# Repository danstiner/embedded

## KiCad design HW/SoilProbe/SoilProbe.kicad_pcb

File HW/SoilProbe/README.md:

# Soil Probe 2026v1

Capacitive soil-moisture probe: a 20 x 126 mm 4-layer blade with the sensing electrodes buried
on the inner layers and a 80-130 MHz LC oscillator in the head. A host MCU (nRF54L15 node)
powers it for a few milliseconds and reads three things:

| Output | What it is | Used for |
|---|---|---|
| `FOUT` | oscillator frequency / 1024, 79 kHz (water) to 126 kHz (air) | volumetric water content |
| `REF - AMP` | oscillation amplitude detector, 8-80 mV | probe loss: bulk EC, salinity correction |
| `NTC` | 10 k thermistor at the soil line | soil temperature, water-permittivity correction |

Nothing has been built yet. Every number here is from simulation (`sim/soil_probe/`), and
`sim/soil_probe/TEST_PLAN.md` lists what to measure first. Design reasoning is in
`sim/soil_probe/DESIGN.md`.

## Predicted performance

| Item | Value | Source |
|---|---|---|
| Range | air to water; soil theta 0-0.6 | `system_sim.py` |
| Error, 2-point calibrated unit, generic medium curve | 1.4 % VWC sd (potting mix), 0.9 % (mineral soil), contact-limited | Monte Carlo, `system_sim.py` |
| Same unit without its own air/water calibration | 2.7 % VWC sd | Monte Carlo |
| Pore-water EC 0.5 to 3 dS/m, frequency only | +0.7 % VWC at theta 0.25, +3 % at 0.55 | error budget |
| Same, using the detector | under 0.1 % | error budget |
| Air gap 0.1 mm on one face | -1.9 % VWC at theta 0.25, -4.4 % at 0.40 | error budget |
| Bulk EC estimate | about +/-12 % (model; the detector is uncalibrated hardware) | Monte Carlo |
| Stops oscillating above | 16 mS probe loss: pore-water EC over about 4 dS/m in saturated potting mix (6 dS/m still runs at theta 0.45) | `characterize.py` |
| Supply | 3.0-3.6 V, about 26 mA for 4 ms per reading (about 100 uC) | datasheet sums |

The contact terms dominate and no circuit fixes them: install the blade in firm, undisturbed
or re-packed soil and do not rock it.

## Host interface (J1, 2.54 mm header pads, wires soldered and potted)

| Pin | Name | Direction | Notes |
|---|---|---|---|
| 1 | VDD | in | 3.0-3.6 V. The LDO is in dropout below 3.1 V, which is fine: frequency moves 190 ppm per 1.5 % of supply |
| 2 | EN | in | high = measure. 1 M pull-down on board |
| 3 | GND | | |
| 4 | NTC | out | 10 k B3380 to GND. Read against a host pull-up, ratiometric to host VDD |
| 5 | AMP | out | detector, 10 k source with 10 nF |
| 6 | REF | out | detector reference, 10 k source with 10 nF. Use `REF - AMP` |
| 7 | FOUT | out | 3.0 V CMOS square wave through 100 R |

Reading sequence:

1. EN high, wait 3.5 ms: LDO start-up is 2.8 ms max (TPS7A05 datasheet), the detector filter
   settles in 0.5 ms.
2. Time 64 periods of FOUT with a TIMER capture on a GPIOTE event (about 0.6 ms, 1e-4
   resolution at 16 MHz). Do not count edges in a TIMER through DPPI at MHz rates; that path
   drops events, which is why the prescaler divides all the way to 100 kHz.
3. Sample AMP, REF and NTC with the SAADC.
4. EN low. No FOUT edges within 1 ms of step 2 means the oscillator is stalled (soil too
   saline and wet): report that instead of a number.

Conversion (details and the reference model in `sim/soil_probe/scripts/system_sim.py`):

- per unit, once: store `f_air`, `f_water`, `det_air` from readings in air and in clean water;
- `x = (f^-2 - f_air^-2) / (f_water^-2 - f_air^-2)`, `q = (REF - AMP) / det_air`;
- `(x, q)` to permittivity and bulk EC through a 2-D table common to all units;
- permittivity to water content with the medium's mixing curve, using the water permittivity at
  the NTC temperature.

## Bill of materials

Passives are 0402 unless noted; any manufacturer.

| Ref | Value | Part | Notes |
|---|---|---|---|
| U1 | 3.0 V LDO, enable | TPS7A0530PDBVR | SOT-23-5. Power gate and regulator in one |
| U2 | 2.5 ns comparator | TLV3601DBVR | SOT-23-5. Squares the 0.1-0.4 V tank signal |
| U3, U4 | D flip-flop | SN74LVC1G80DBVR | SOT-23-5. Divide by 4; 160 MHz guaranteed |
| U5 | 12-stage ripple counter | SN74LV4040APWR | TSSOP-16. Q8 used, divide by 256 |
| Q1, Q2, Q3 | NPN RF, fT 8 GHz, Ccb 0.3 pF | BFR181 | SOT-23. Low Ccb and transit time set the loss pulling; do not substitute a general-purpose NPN |
| L1, L2 | 22 nH 2 %, Q >= 40 at 250 MHz | LQW18AN22NG00 | 0603 wirewound |
| C4 | 33 pF C0G 2 % | any | tank capacitor |
| R3 | 15 R 1 % | any | in series with C4: damps the strip line's second resonance |
| R4, R5, R7 | 22 R 1 % | any | base stoppers |
| R6 | 560 R 1 % | any | tail current, 3.1 mA |
| R8 | 1.1 k 1 % | any | reference transistor at half the tail current |
| R2 | 100 R 1 % | any | collector feed, sets the comparator common mode |
| R11, R12, R13 | 100 R | any | comparator input isolation, FOUT series |
| R9, R10 | 10 k | any | detector filters |
| R1 | 1 M | any | EN pull-down |
| C3, C5, C6 | 10 nF | any | |
| C7-C10 | 100 nF | any | |
| C1, C2 | 1 uF 0603 | any | LDO in and out |
| TH1 | 10 k NTC 1 %, B 3380 | NCP15XH103F03RC | |
| J1 | 1x7 2.54 mm pads | none | solder wires |

## Fabrication

OSH Park 4-layer: FR408HR, 0.2 mm 2113 prepreg over the inner layers, ENIG. The board stackup
in the `.kicad_pcb` matches their published one, and the design rules in the `.kicad_pro` are
their 4-layer limits (5 mil track and space, 10 mil drill, 4 mil annular ring, 10 mil hole to
inner copper).

The prepreg is part of the sensor: it is the 0.2 mm insulation between electrode and soil, and
its thickness tolerance (+/-10 %) is the main unit-to-unit term left after calibration (about
0.5 % VWC). A fab with a different outer prepreg works but shifts the common table: rerun the
simulation with that stack.

The sensing area has no copper on the outer layers and no vias, so nothing metallic touches
the soil even if the mask is scratched.

## Assembly and potting

- Parts are on the front only. There are no reference designators on the silkscreen (no room
  between the 0402s); use the fab layer or the interactive placement in KiCad.
- Pot the head on both faces down to the SOIL LINE mark. The simulation assumes potting
  compound (relative permittivity about 3.5) over the 6 mm of strip above the soil line; the
  two-point calibration absorbs the difference if you use something else, as long as it is
  applied before calibrating.
- Seal the board edges of the blade (conformal coat or a thin epoxy wipe). The strips stop 1 mm
  short of the edge, but exposed FR-4 edges wick water along the glass weave over time.
- Calibrate after potting: one reading in air, one with the blade in clean water up to the soil
  line.

## Bring-up, before any soil

Predicted values from `sim/soil_probe/scripts/expected_liquids.py`:

| Medium | FOUT | REF - AMP |
|---|---|---|
| air | 126.0 kHz | 40 mV |
| isopropanol 99 % | 102.1 kHz | 60 mV |
| tap water (0.3 mS/cm) | 79.6 kHz | 62 mV |
| 1 g/L salt water | 77.9 kHz | 20 mV |

Absolute frequency depends on stray capacitance that the simulation only estimates (2.5 pF per
tank node); expect the air value within +/-5 %. The ratios between media are the real test. If
FOUT in air is above 137 kHz the first flip-flop is being clocked past 140 MHz: raise C4.

Never probe the tank nodes (SA, SB) with a scope probe; 10 pF moves the oscillator 10 %. Look
at FOUT, or at the comparator output with a low-capacitance probe.

## Files

| Path | Contents |
|---|---|
| `SoilProbe.kicad_sch`, `.kicad_pcb`, `.kicad_pro` | KiCad 10 project. ERC and DRC (with schematic parity) are clean |
| `Components/SoilProbe.kicad_sym` | comparator and probe-strip symbols |
| `sim/soil_probe/` | field solver, probe line model, ngspice oscillator model, system simulation, design notes, test plan |

The schematic and board were generated by script from one netlist and then checked with
`kicad-cli`; they are ordinary KiCad files and are meant to be edited by hand from here on.

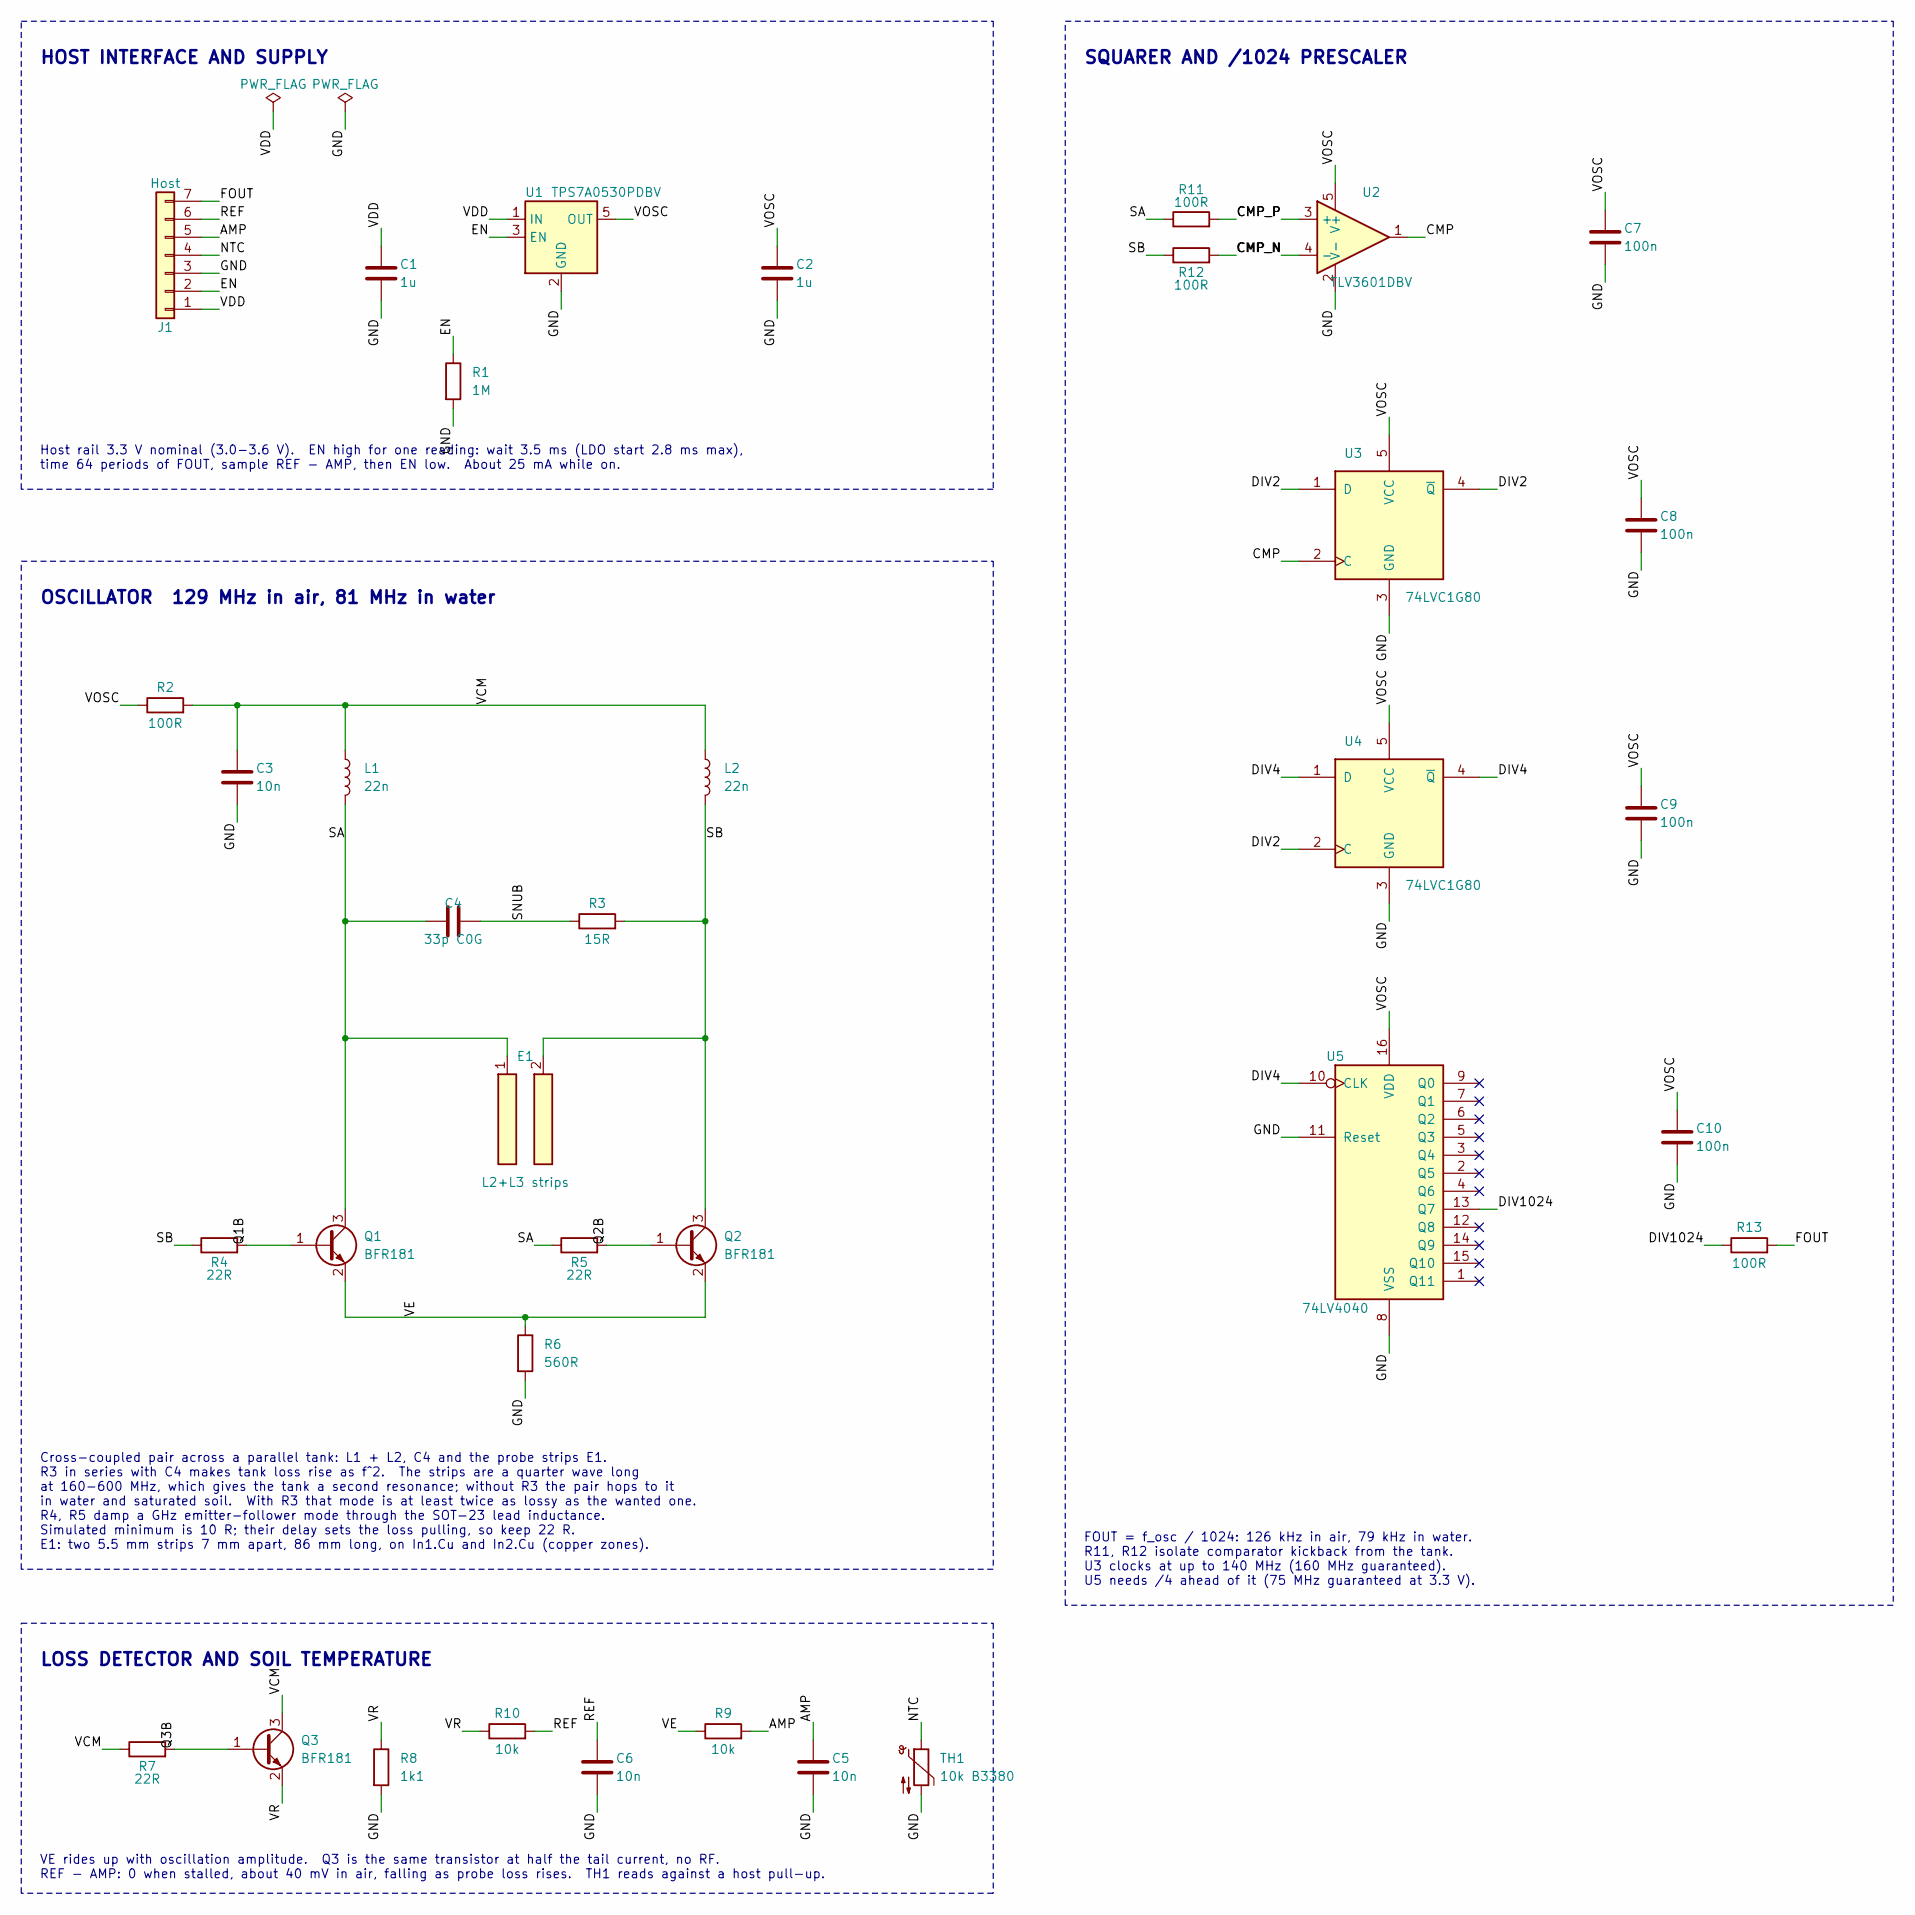
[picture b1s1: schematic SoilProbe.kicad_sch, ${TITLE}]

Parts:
C1, C2: 1u; C_0603_1608Metric
C3, C5, C6: 10n; C_0402_1005Metric
C4: 33p C0G; C_0402_1005Metric; Tolerance 2%
C7, C8, C9, C10: 100n; C_0402_1005Metric
E1: L2+L3 strips
J1: Host; PinHeader_1x07_P2.54mm_Vertical
L1, L2: 22n; L_0603_1608Metric; Tolerance 2%; MPN LQW18AN22NG00D
Q1, Q2, Q3: BFR181; SOT-23; MPN BFR181E6327HTSA1
R1: 1M; R_0402_1005Metric
R2: 100R; R_0402_1005Metric; Tolerance 1%
R3: 15R; R_0402_1005Metric; Tolerance 1%
R4, R5, R7: 22R; R_0402_1005Metric; Tolerance 1%
R6: 560R; R_0402_1005Metric; Tolerance 1%
R8: 1k1; R_0402_1005Metric; Tolerance 1%
R9, R10: 10k; R_0402_1005Metric
R11, R12, R13: 100R; R_0402_1005Metric
TH1: 10k B3380; R_0402_1005Metric; Tolerance 1%; MPN NCP15XH103F03RC
U1: TPS7A0530PDBV; SOT-23-5; MPN TPS7A0530PDBVR
U2: TLV3601DBV; SOT-23-5; MPN TLV3601DBVR
U3, U4: 74LVC1G80; SOT-23-5; MPN SN74LVC1G80DBVR
U5: 74LV4040; TSSOP-16_4.4x5mm_P0.65mm; MPN SN74LV4040APWR

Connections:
/AMP: C5.1, J1.5, R9.2
/CMP: U2.1, U3.2 (C)
/CMP_N: R12.2, U2.4 (-)
/CMP_P: R11.2, U2.3 (+)
/DIV2: U3.1 (D), U3.4 (~Q), U4.2 (C)
/DIV4: U4.1 (D), U4.4 (~Q), U5.10 (CLK)
/DIV1024: R13.1, U5.13 (Q7)
/EN: J1.2, R1.1, U1.3 (EN)
/FOUT: J1.7, R13.2
/GND: C1.2, C2.2, C3.2, C5.2, C6.2, C7.2, C8.2, C9.2, C10.2, J1.3, R1.2, R6.2, R8.2, TH1.2, U1.2 (GND), U2.2 (V-), U3.3 (GND), U4.3 (GND), U5.8 (VSS), U5.11 (Reset)
/NTC: J1.4, TH1.1
/Q1B: Q1.1 (B), R4.2
/Q2B: Q2.1 (B), R5.2
/Q3B: Q3.1 (B), R7.2
/REF: C6.1, J1.6, R10.2
/SA: C4.1, E1.1 (A), L1.2, Q1.3 (C), R5.1, R11.1
/SB: E1.2 (B), L2.2, Q2.3 (C), R3.2, R4.1, R12.1
/SNUB: C4.2, R3.1
/VCM: C3.1, L1.1, L2.1, Q3.3 (C), R2.2, R7.1
/VDD: C1.1, J1.1, U1.1 (IN)
/VE: Q1.2 (E), Q2.2 (E), R6.1, R9.1
/VOSC: C2.1, C7.1, C8.1, C9.1, C10.1, R2.1, U1.5 (OUT), U2.5 (V+), U3.5 (VCC), U4.5 (VCC), U5.16 (VDD)
/VR: Q3.2 (E), R8.1, R10.1

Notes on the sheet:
HOST INTERFACE AND SUPPLY
Host rail 3.3 V nominal (3.0-3.6 V). EN high for one reading: wait 3.5 ms (LDO start 2.8 ms max), time 64 periods of FOUT, sample REF - AMP, then EN low. About 25 mA while on.
OSCILLATOR 129 MHz in air, 81 MHz in water
Cross-coupled pair across a parallel tank: L1 + L2, C4 and the probe strips E1. R3 in series with C4 makes tank loss rise as f^2. The strips are a quarter wave long at 160-600 MHz, which gives the tank a second resonance; without R3 the pair hops to it in water and saturated soil. With R3 that mode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
LOSS DETECTOR AND SOIL TEMPERATURE
VE rides up with oscillation amplitude. Q3 is the same transistor at half the tail current, no RF. REF - AMP: 0 when stalled, about 40 mV in air, falling as probe loss rises. TH1 reads against a host pull-up.
SQUARER AND /1024 PRESCALER
FOUT = f_osc / 1024: 126 kHz in air, 79 kHz in water. R11, R12 isolate comparator kickback from the tank. U3 clocks at up to 140 MHz (160 MHz guaranteed). U5 needs /4 ahead of it (75 MHz guaranteed at 3.3 V).

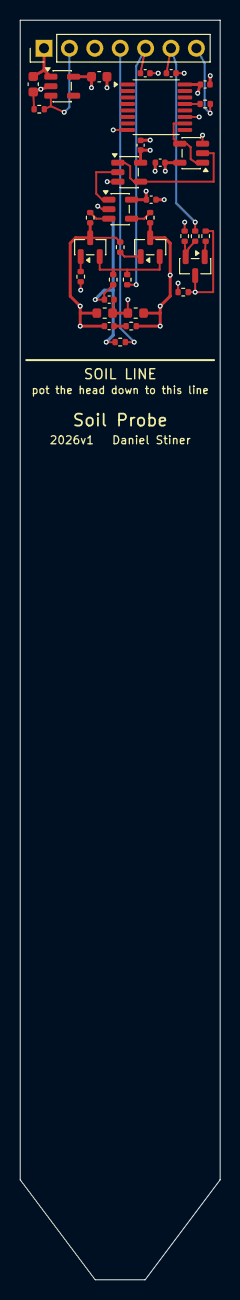
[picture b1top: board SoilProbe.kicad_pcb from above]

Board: 4 copper layers, 20.0 x 126.0 mm, 35 parts (0 on the bottom side), 23 nets.

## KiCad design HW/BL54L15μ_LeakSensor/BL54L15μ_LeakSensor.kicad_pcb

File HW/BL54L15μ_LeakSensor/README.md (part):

# Leak sensor

## 1. Scope

Battery-powered leak and humidity sensor built on the Ezurio BL54L15μ (nRF54L15) module.
Two contacts on the bottom detect water, immediately triggering a report over Matter
and optionally an alarm buzzer. An SHT40 measures temperature and humidity for mold detection.

The board stands on the end of a CR2 cell in a printed case. Two metal pins in the case's
floor touch the water and press on two dome contacts on the board (5.7).

This is revision **2026v5**, ordered on 2026-11-23 (tag `fab/BL54L15μ-leak-sensor/2026v5`)
and not yet assembled. The baseline is 2026v4, the first leak board,
fabricated as the hygrometer's 2026v4 (tag `fab/BL54L15μ-hygrometer/2026v4`, firmware
board `bl54l15u_hygrometer@2026v4`).

## 2. Changes from 2026v4

| Item          | 2026v4                                   | 2026v5                                                  |
| ------------- | ---------------------------------------- | ------------------------------------------------------- |
| Size          | 48 mm circle                             | 18 × 16 mm, stands on the end of the cell (5.6)         |
| Battery       | CR2 in a Keystone 1011 holder            | CR2 on wires to two pads on the back                    |
| Leak contacts | 6 mm domes on the back, driven one way   | 4 mm domes on the front, driven either way (4.1)        |
| Leak pins     | drive P0.01, sense P1.07, 1 MΩ to ground | P1.12 and P1.11 each drive or sense; 1 MΩ to a GPIO     |
| Sensor        | SHT45                                    | SHT40 (5.3)                                             |
| I2C           | SDA P1.14, SCL P1.04                     | unchanged                                               |
| Buzzer        | 8.5 mm, never driven by firmware         | 5 mm, on P1.05, smaller driver parts (5.5)              |
| SWD           | 2×5 1.27 mm box header on the front      | 2×5 1.27 mm pads on the back: header or pogo clip (4.2) |
| Mounting      | two holes                                | none; the case holds the board by its edge              |

## 3. Requirements

| ID  | Requirement                                                                             |
| --- | --------------------------------------------------------------------------------------- |
| R-1 | Wake on water across the contacts: Edge triggered, not polling                          |
| R-2 | Last 5 years on one CR2 (850 mAh): average current under 15 µA assuming 20% derating    |
| R-3 | Minimize probe corrosion: alternate probe voltage                                       |
| R-4 | Confirm water by measuring resistance with the SAADC, in both directions                |
| R-5 | Temperature and humidity reports from SHT4x over I2C with MCU pull-ups                  |
| R-6 | Minimize case size with small board standing on the end of a CR2 (Ø15.6 max)            |
| R-7 | SWD through a soldered 2×5 1.27 mm header or a pogo-pin clip from the side              |
| R-8 | Front parts in one reflow pass; the back has only pads and optional parts (J1, JP1, C3) |
| R-9 | A buzzer that can optionally sound when it finds water, >=60 dBA at 1 m                 |

## 4. Design trades

### 4.1 Leak front end

2026v4 drives one contact through 10 kΩ and senses the other through 10 kΩ, with 1 MΩ to
ground. While dry the drive is held high: no current flows, and a rising edge on the sense
pin wakes the board. Current always flows the same way, which polarizes the contacts and
corrodes the anode. Conductivity cells are driven with alternating polarity for this
reason (Lee and Kester, Analog Dialogue 50-11).

2026v5 makes both sides identical, so either can drive and either can sense:

- **1 MΩ returned to a GPIO, not ground.** While armed, the driving side's 1 MΩ would
  otherwise sit across the cell and draw 3 µA, 20 % of R-2. With its return pin at the
  same level as the drive it draws nothing.
- **Two return pins, not one.** One shared return cannot sit high for the driving side and
  low for the sensing side at the same time.
- **External pull-down.** At the nRF54L15's 13 kΩ typical internal pull-down (Ezurio
  datasheet, I2C note) the sense node could never reach the input-high level through
  20 kΩ of series resistance.
- **Both sense pins analog-capable** (AIN5, AIN4), since each side senses in one direction.

### 4.2 Debug connector

A 2×5 1.27 mm box header (CNC Tech 3220-10-0300-00, 4.9 mm tall) on the back would hold
the cell 5 mm off the board. So J1 is a set of pads that takes either that header,
hand-soldered on the first few boards, or a pogo-pin clip clamped on from the left edge.
The case is sized for boards without the header.

Standard header land patterns start at the pin rows, 0.635 mm off center, and run outward
under the bent tails: 0.63 to 3.40 mm in the header's datasheet, 0.75 to 3.15 mm in
KiCad's stock footprint. A clip whose rows are 1.27 mm apart would land on the very ends
of those pads. J1's pads start 0.3 mm off center, so they take clip rows 1.27 or 2.54 mm
apart as well as the header's tails (`Components/LeakSensor.pretty`). The pads on the
edge side stop at 2.6 mm to keep copper 0.381 mm from the edge; the header's tails
overhang them by about 0.15 mm, with no fillet at the toe.

BZ1 sits on the front directly opposite J1, so the clip's other jaw rests on its flat
top. No keep-out is reserved for the clip: it presses lightly and tolerates an uneven
bite.

### 4.3 Supply

The CR2 feeds everything directly: the module takes 1.7 to 3.5 V (Ezurio datasheet 0.7,
table 3) and the SHT40 1.08 to 3.6 V. The firmware reads the cell through the SAADC's VDD
input. There is no reverse-polarity protection; the wires are soldered once.

## 5. Circuit

### 5.1 Leak front end: P1, P2, D1, D2, R1–R4

```
P1 ── ELEC_A ──┬── R1 10 kΩ ── LEAK_A (P1.12, AIN5) ── R3 1 MΩ ── LEAK_A_RET (P1.09)
               D1 TPD1E10B06 to GND
P2 ── ELEC_B ──┬── R2 10 kΩ ── LEAK_B (P1.11, AIN4) ── R4 1 MΩ ── LEAK_B_RET (P1.10)
               D2 TPD1E10B06 to GND
```

| State (A to B; B to A swaps the sides) | LEAK_A   | LEAK_A_RET | LEAK_B           | LEAK_B_RET | Current while dry |
| -------------------------------------- | -------- | ---------- | ---------------- | ---------- | ----------------- |
| Armed                                  | out high | out high   | input, edge wake | out low    | none              |
| Measure                                | out high | out high   | SAADC            | out low    | none              |
| Parked (after water is found)          | out low  | out low    | out low          | out low    | none              |

- **Wake threshold.** The sensing node sits at VDD × R4 / (R4 + R1 + R2 + R_water), which
  does not depend on the cell voltage. With V_IH = 0.7 VDD (to be confirmed in the nRF54L15
  datasheet) the edge fires below about 0.41 MΩ between the contacts.
- **SAADC.** The same divider reads 0.27 V at 10 MΩ, so damp contacts well above the wake
  threshold are still seen (`CONFIG_APP_LEAK_THRESHOLD_MV`). Averaging the two directions
  cancels the contacts' polarization offset.
- **Wet and armed**, at most VDD / 1.02 MΩ ≈ 3 µA flows one way until the firmware parks
  the pins.
- R1 and R2 limit current into the pins; D1 and D2 clamp ESD at the contacts.

### 5.2 MCU module: Ezurio 453-00223R (IC1)

| Pad    | nRF54L15      | Net        | Use                                               |
| ------ | ------------- | ---------- | ------------------------------------------------- |
| 5      | VDD           | VDD        | C2 10 µF, the one capacitor Ezurio requires (5.1) |
| 19     | P1.12 / AIN5  | LEAK_A     | Contact A: drive, edge wake, SAADC                |
| 23     | P1.11 / AIN4  | LEAK_B     | Contact B                                         |
| 22     | P1.09         | LEAK_A_RET | R3's return                                       |
| 21     | P1.10         | LEAK_B_RET | R4's return                                       |
| 18, 17 | P1.14, P1.04  | SDA, SCL   | U1 (firmware `i2c21`), internal pull-ups          |
| 15     | P1.05         | BUZZ       | Q1's gate: BZ1 at 4 kHz (5.5)                     |
| 12, 10 | P1.00, P1.01  | XL1, XL2   | X1, 32.768 kHz, internal load capacitors          |
| 27, 25 | SWDIO, SWDCLK | –          | J1 2, 4                                           |
| 32     | nRESET        | –          | J1 10                                             |
| 42     | P2.07         | SWO        | J1 6                                              |

- **Nordic's pin rules** decide which pins can be used: a peripheral reaches pins of its
  own port only, so I2C and PWM are on port 1; port 2 cannot wake the chip; SCL must be on
  a clock pin (Nordic DevZone, section 9). Within those rules the pads are taken in the
  order the traces leave the module: I2C toward U1, then the leak nets.
- **LEAK_A_RET** takes inner pad 22 and a via under the module, as a fourth net cannot
  leave the bottom pad row on the front. It is a static line.
- **Analog channels.** The AIN numbers are from the Ezurio pin table. 2026v4 confirmed
  P1.07 = AIN3 on hardware; AIN4 and AIN5 are unconfirmed (section 8). A wrong channel
  reads near VDD, which looks like a leak.
- **Firmware** sees this in a new board revision's overlay: the leak node's four pins and
  two SAADC channels, and the buzzer as a PWM on P1.05. The I2C pins are 2026v4's.
- All other pins are open and flagged no-connect. The module's DC/DC inductor is inside.

### 5.3 Temperature and humidity: SHT40-AD1F (U1)

U1 is at address 0x44 with C1 100 nF beside it, on I2C through the module's 13 kΩ
pull-ups. It is typically within ±1.8 %RH and ±0.2 °C (SHT4x datasheet, tables 1 and 2),
enough to watch for mold; 2026v4's SHT45 was more accurate than needed. The AD1F version
has a membrane over the sensor opening. Idle current is 0.08 µA typical (table 4).

Self-heating is negligible: the board averages about 0.05 mW. What matters is how freely
room air reaches U1. The case has one small vent beside it (5.7), so U1 follows the room
slowly. BZ1 is 2 mm away, so an alarm warms U1 for some minutes (7.1).

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
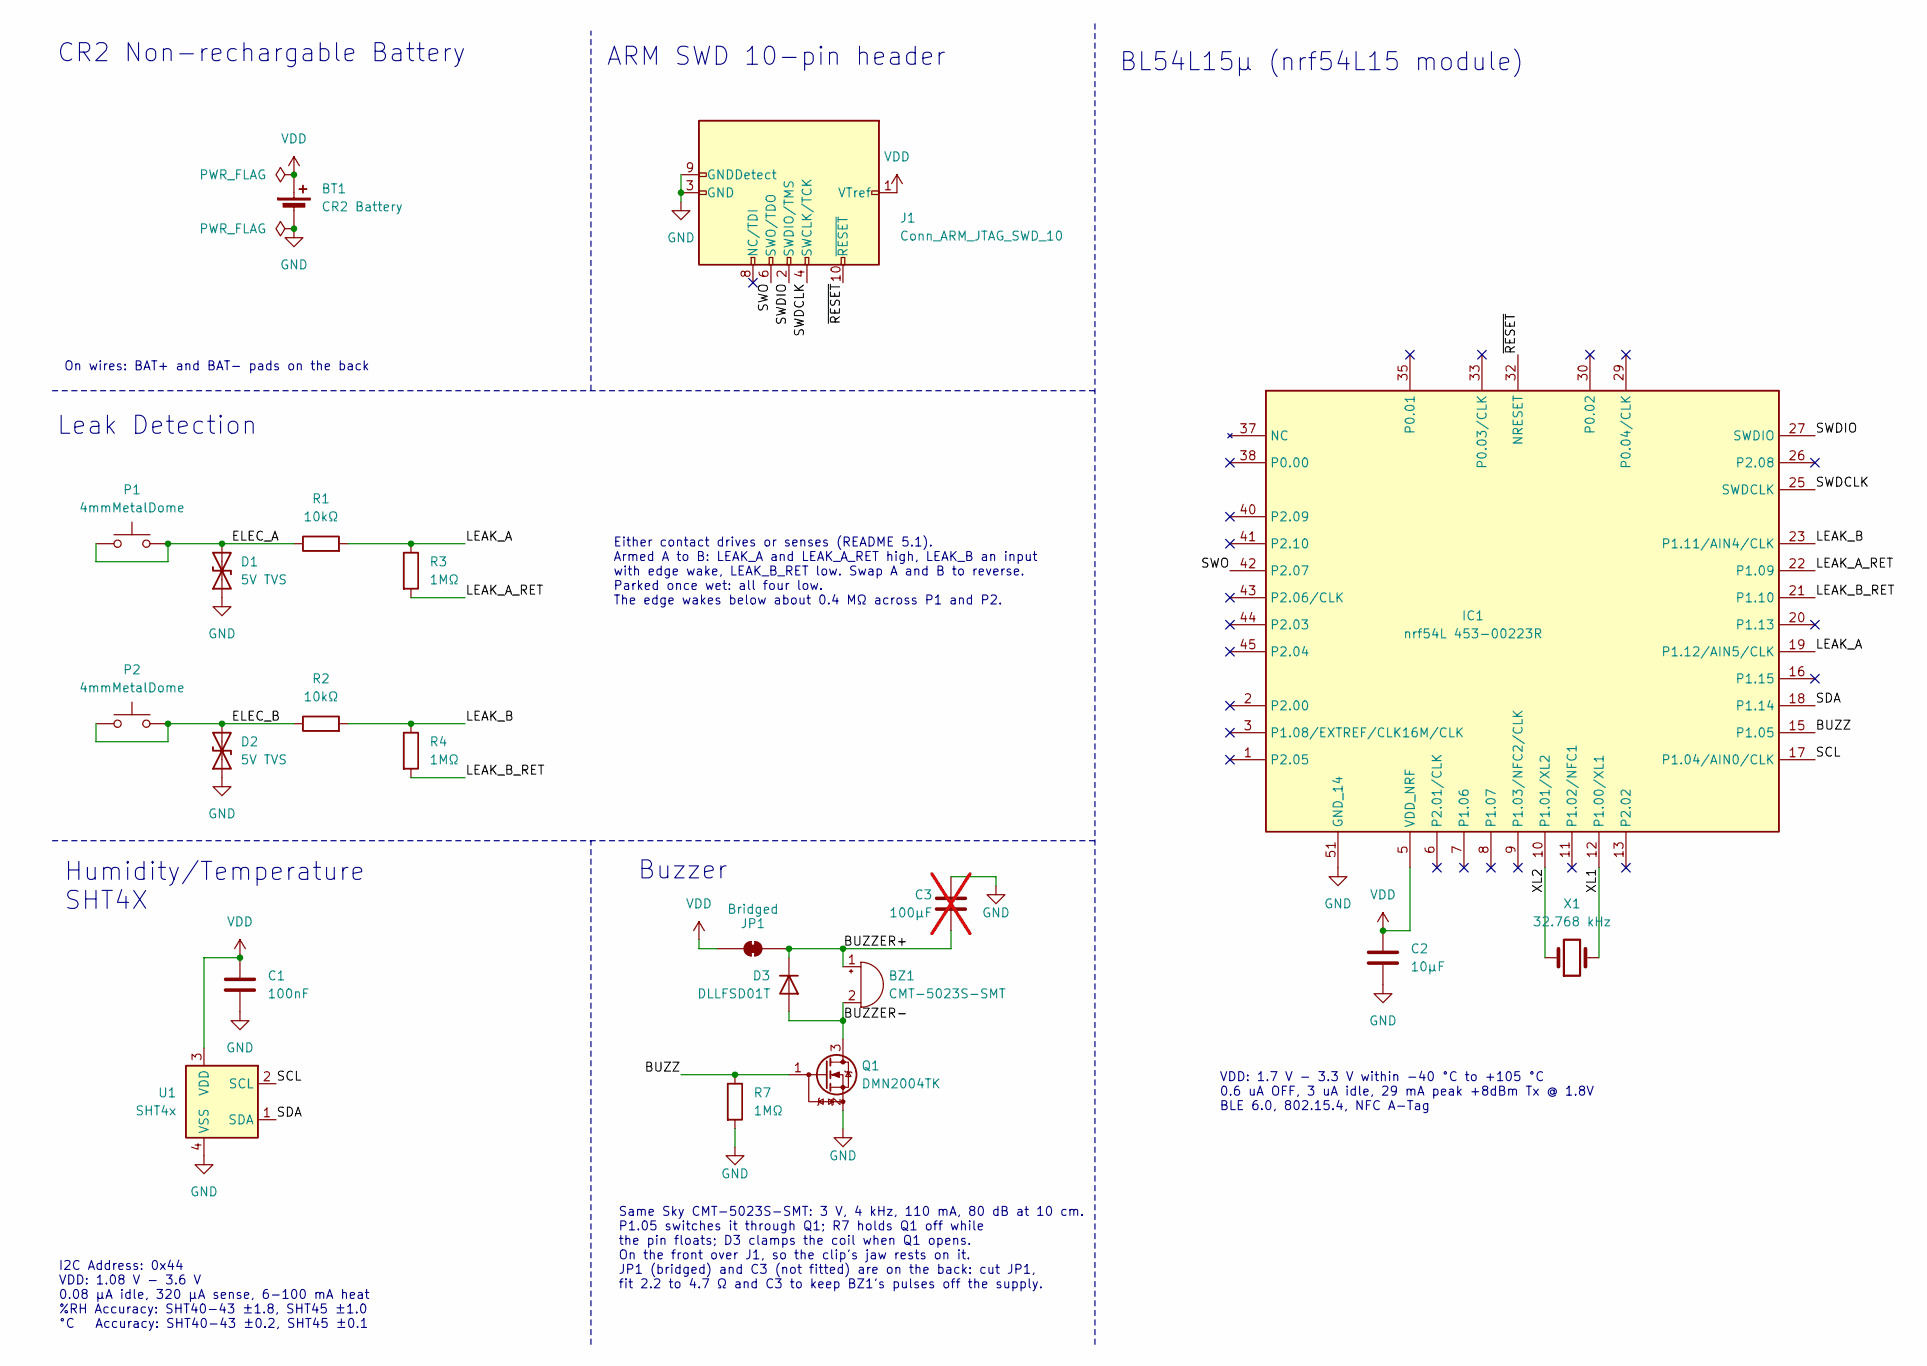
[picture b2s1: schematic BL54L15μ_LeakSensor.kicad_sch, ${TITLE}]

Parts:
BT1: CR2 Battery; CR2_WirePads_D2.0mm_P2.5mm
BZ1: CMT-5023S-SMT; Buzzer_CUI_CMT-5023S-SMT; Part Number CMT-5023S-SMT-TR
C1: 100nF; C_0402_1005Metric; Part Number GRM155R61A104KA01J
C2: 10μF; C_0603_1608Metric; Part Number CL10A106KP8NNNC
C3: 100μF; C_1206_3216Metric_NoSilk; not fitted
D1, D2: 5V TVS; D_0402_1005Metric; Part Number TPD1E10B06DPYR
D3: DLLFSD01T; D_SOD-523; Part Number DLLFSD01T-7
IC1: nrf54L 453-00223R; 45300223R; Part Number 453-00223R; Digikey Part Number 776-453-00223RCT-ND
J1: Conn_ARM_JTAG_SWD_10; SWD_2x05_P1.27mm_HeaderOrPogo; Part Number 3220-10-0300-00
JP1: Bridged; R_0402_Bridged
P1, P2: 4mmMetalDome; TriangleDome_Diameter4mm; Part Number 4 mm metal dome, part TBD
Q1: DMN2004TK; SOT-523; Part Number DMN2004TK-7
R1, R2: 10kΩ; R_0402_1005Metric; Part Number RC0402FR-0710KL
R3, R4, R7: 1MΩ; R_0402_1005Metric; Part Number RC0402FR-071ML
U1: SHT4x; Sensirion_DFN-4_1.5x1.5mm_P0.8mm_SHT4x_NoCentralPad_Stacked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; Part Number SHT40-AD1F-R2
X1: 32.768 kHz; XTAL_CM7V-T1A-LOW-ESR-32.768KHZ-9PF-20-TA-QC; Part Number CM7V-T1A-LOW-ESR-32.768KHZ-9PF-20-TA-QC; Digikey Part Number 2195-CM7VT1ALOWESR32.768KHZ9PF20TAQCCT-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

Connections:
/BUZZ: IC1.15 (P1.05), Q1.1 (G), R7.1
/BUZZER+: BZ1.1 (+), C3.2, D3.1 (K), JP1.2 (B)
/BUZZER-: BZ1.2 (-), D3.2 (A), Q1.3 (D)
/ELEC_A: D1.2 (A2), P1.1, P1.2, R1.1
/ELEC_B: D2.2 (A2), P2.1, P2.2, R2.1
/LEAK_A: IC1.19 (P1.12/AIN5/CLK), R1.2, R3.1
/LEAK_A_RET: IC1.22 (P1.09), R3.2
/LEAK_B: IC1.23 (P1.11/AIN4/CLK), R2.2, R4.1
/LEAK_B_RET: IC1.21 (P1.10), R4.2
/SCL: IC1.17 (P1.04/AIN0/CLK), U1.2 (SCL)
/SDA: IC1.18 (P1.14), U1.1 (SDA)
/SWDCLK: IC1.25 (SWDCLK), J1.4 (SWCLK/TCK)
/SWDIO: IC1.27 (SWDIO), J1.2 (SWDIO/TMS)
/SWO: IC1.42 (P2.07), J1.6 (SWO/TDO)
/XL1: IC1.12 (P1.00/XL1), X1.2
/XL2: IC1.10 (P1.01/XL2), X1.1
/~RESET: IC1.32 (NRESET), J1.10 (~RESET)
GND: BT1.2 (-), C1.2, C2.2, C3.1, D1.1 (A1), D2.1 (A1), IC1.4 (GND_1), IC1.14 (GND_2), IC1.24 (GND_3), IC1.28 (GND_4), IC1.31 (GND_5), IC1.34 (GND_6), IC1.36 (GND_7), IC1.39 (GND_8), IC1.46 (GND_9), IC1.47 (GND_10), IC1.48 (GND_11), IC1.49 (GND_12), IC1.50 (GND_13), IC1.51 (GND_14), J1.3 (GND), J1.5 (GND), J1.9 (GNDDetect), Q1.2 (S), R7.2, U1.4 (VSS)
VDD: BT1.1 (+), C1.1, C2.1, IC1.5 (VDD_NRF), J1.1 (VTref), JP1.1 (A), U1.3 (VDD)

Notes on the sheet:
VDD: 1.7 V - 3.3 V within -40 °C to +105 °C 0.6 uA OFF, 3 uA idle, 29 mA peak +8dBm Tx @ 1.8V BLE 6.0, 802.15.4, NFC A-Tag
Either contact drives or senses (README 5.1). Armed A to B: LEAK_A and LEAK_A_RET high, LEAK_B an input with edge wake, LEAK_B_RET low. Swap A and B to reverse. Parked once wet: all four low. The edge wakes below about 0.4 MΩ across P1 and P2.
CR2 Non-rechargable Battery
Humidity/Temperature SHT4X
On wires: BAT+ and BAT- pads on the back
Same Sky CMT-5023S-SMT: 3 V, 4 kHz, 110 mA, 80 dB at 10 cm. P1.05 switches it through Q1; R7 holds Q1 off while the pin floats; D3 clamps the coil when Q1 opens. On the front over J1, so the clip's jaw rests on it. JP1 (bridged) and C3 (not fitted) are on the back: cut JP1, fit 2.2 to 4.7 Ω and C3 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
Leak Detection
Buzzer
BL54L15μ (nrf54L15 module)
I2C Address: 0x44 VDD: 1.08 V - 3.6 V 0.08 μA idle, 320 μA sense, 6-100 mA heat %RH Accuracy: SHT40-43 ±1.8, SHT45 ±1.0 °C Accuracy: SHT40-43 ±0.2, SHT45 ±0.1
ARM SWD 10-pin header

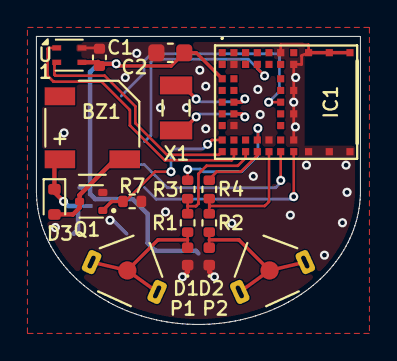
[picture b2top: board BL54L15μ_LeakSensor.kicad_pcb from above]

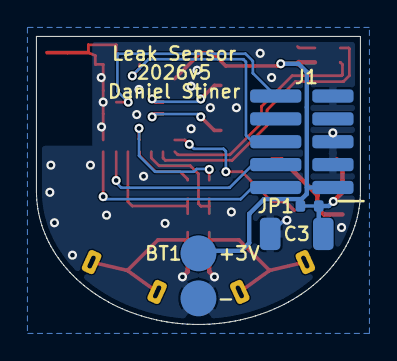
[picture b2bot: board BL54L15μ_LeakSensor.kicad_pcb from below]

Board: 2 copper layers, 18.0 x 16.0 mm, 21 parts (4 on the bottom side), 19 nets.

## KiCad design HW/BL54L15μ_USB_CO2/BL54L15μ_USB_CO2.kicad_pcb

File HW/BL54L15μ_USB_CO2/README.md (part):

# USB CO2 sensor

## 1. Scope

A USB-powered indoor air sensor built on the Ezurio BL54L15μ (nRF54L15) module. It measures
CO2 with a Sensirion SCD43, temperature and humidity with an SHT4x, and pressure and gas
resistance with a BME68x. It joins a Thread network as an always-on router.

Revision 2026v2 is in progress: the SHT4x moves from 2026v1's slotted island onto a zigzag
finger cut from the board's left edge (5.5, 5.9), and its traces are not routed yet.
2026v1 was ordered on 2026-11-21 and is tagged `fab/BL54L15μ-usb-co2/2026v1`.

## 2. Background

This board aims to be an accurate, set and forget CO2 sensor. No battery that needs replacement.

Programming and the serial console use the USB-C receptacle that powers the board, with
the pinout of `HW/BL54L15μ_DevKit` mirrored, so `HW/SWD_USBC_InlineAdapter` works
unchanged, plugged in the other way up (5.1).

## 3. Requirements

| ID   | Requirement                                                                         |
| ---- | ----------------------------------------------------------------------------------- |
| R-1  | Report CO2 every 30 s, accuracy at least ±(50 ppm + 3 %) over 400 to 5000 ppm       |
| R-2  | Report temperature and humidity every 30 s, accuracy at least ±0.2 °C and 2 %RH     |
| R-4  | Run from any 5 V USB-C source, drawing under 500 mA peak                            |
| R-5  | Keep the radio powered continuously (Thread router); no battery                     |
| R-6  | SWD, reset, SWO and a UART on the USB-C receptacle, for the DevKit's adapter        |
| R-7  | CO2 sensor supply: holds 205 mA peaks, moves less than 30 mV because of other loads |
| R-9  | Fit a small square enclosure with rounded corners; USB and vents on the rear face   |
| R-10 | Single-sided surface-mount assembly, one reflow pass on a hot plate, no board wash  |
| R-11 | Keep the sensor bus the hygrometer firmware already uses: same pins, MCU pull-ups   |
| R-12 | Module supply: ripple and noise under 10 mV, the limit for an undisturbed radio     |

## 4. Design trades

### 4.1 CO2 sensor

|                          | STCC4                          | SCD41                        | **SCD43**            |
| ------------------------ | ------------------------------ | ---------------------------- | -------------------- |
| Principle                | thermal conductivity           | photoacoustic                | photoacoustic        |
| Accuracy, 400–5000 ppm   | ±(100 ppm + 10 %)              | ±(50 ppm + 2.5 %) ¹          | ±(30 ppm + 3 %)      |
| Average current at 3.3 V | 0.95 mA continuous, 0.1 mA single shot every 10 s | 15 mA periodic, 3.2 mA low power periodic | same as SCD41 |
| Peak current at 3.3 V    | 4.2 mA max                     | 205 mA max                   | 205 mA max           |
| Size                     | 4 × 3 × 1.2 mm                 | 10.1 × 10.1 × 6.5 mm         | 10.1 × 10.1 × 6.5 mm |
| Self-calibration         | automatic, expects fresh air once a week | automatic, same expectation | same as SCD41 |
| Warm-up                  | up to 1 h after 3 h unpowered, 12 h on first use | none specified | none specified |

¹ In its 400–1000 ppm band; ±(50 ppm + 3 %) from 1001 to 2000 ppm and ±(40 ppm + 5 %) above.

Sources (section 9): STCC4 datasheet, tables 1 and 3, sections 1.1.2 to 1.1.4 and figure
3; SCD4x datasheet, tables 1 and 4 and section 3.8.

**Chosen: SCD43.** It is the most accurate of the family over the whole range, and with
USB power its 15 mA average and 205 mA peaks are free. The SCD40, SCD41 and SCD43 share one
package, land pattern and command set, so the footprint also takes an SCD41. The unreleased
SCD5x may be a better choice once released, but its specs are not yet known.

### 4.2 USB receptacle

**Chosen: GCT USB4056-03-A**, the DevKit's 24-contact receptacle (surface-mount front row,
through-hole back row). The DevKit puts SWD on the SuperSpeed TX pairs and the UART on an
RX pair (5.1); a 16-contact USB 2.0 receptacle has no contacts there, so only a full one
can carry the same pinout.

### 4.3 Regulation

|                               | **One LDO** | Two LDOs            | Buck              | SCD43 on VBUS       |
| ----------------------------- | ----------- | ------------------- | ----------------- | ------------------- |
| SCD43 rail moved by other loads | under 1 mV | no                  | plus ripple       | USB source noise    |
| MCU rail sees 205 mA pulses   | yes         | no                  | yes               | no                  |
| Parts                         | 3           | 6                   | 5 or more         | 3                   |
| Heat at 48 mA average         | 94 mW       | 94 mW               | about 25 mW       | 60 mW               |
| I2C levels                    | fine        | fine                | fine              | VIH 3.25 V at 5 V   |

Part counts and heat are calculated (an LDO from 5.25 V to 3.3 V at 48 mA dissipates
94 mW); the rest is from the datasheets in section 9.

**Chosen: one AP2112K-3.3 for the whole board.** The SCD4x datasheet (section 2.3) says the
supply "must not vary by more than 30 mV" because of other loads and recommends a separate
LDO, advice aimed at boards where a radio or motor shares the rail. Here the other loads
step by 10 to 30 mA, which the AP2112's worst-case load regulation of 1 %/A turns into
1 mV at most. The SCD43's own 205 mA pulses dip the shared rail, but the SHT4x
(1.08–3.6 V) and BME680 (1.71–3.6 V) do not mind.

The module could, for all its 1.7–3.5 V range: its datasheet (table 3) allows only 10 mV
of ripple or noise on its supply, at any frequency, as the level that does not disturb the radio (R-12). The 205 mA
step moves the output by 1.4 mV typical and 6.8 mV worst case in steady state. The
AP2112's load-transient figure shows about 10 mV for a 0 to 600 mA step with 1 µF on the
output; here the step is a third of that and the rail carries 21 µF, so the dip should be
smaller. That is an estimate, not a measurement (section 7). If it fails, the fixes are a
separate regulator for the SCD43, as Sensirion recommends, or a small resistor ahead of C3
so the module sits behind its own filter.

A buck would save about 25 mW at typical load, about 0.8 °C of the SHT4x's steady offset
(5.9), which firmware subtracts anyway. Feeding the sensor from VBUS
would put the source's noise on it and raise its I2C threshold to 0.65 × VDD (SCD4x
table 4), 3.25 V at 5 V, which a 3.3 V bus only just meets.

## 5. Circuit

```
 J1 USB-C
  VBUS o--+--[R1 1Ω]------+---- VIN ----[U1 AP2112K-3.3]---- VDD --+-- IC1 module
          |               |                                       +-- U2 SCD43
      [D1 clamp]         [C1]                                     +-- U3 SHT4x
          |               |                                       +-- U4 BME68x
  GND  o--+---------------+---- GND                               +-- SBU2 (VTref)
  CC1  o--[R2 5.1k]-- GND
  CC2  o--[R3 5.1k]-- GND                    IC1 P1.14, P1.04 ---- I2C ---- U2, U3, U4
  TX2+/- o--[D1]-- SWDIO, SWDCLK -- IC1      IC1 P2.04 --[R4]--[D2 LED]
  TX1+/- o-- nRESET (JP1), SWO ---- IC1      IC1 P0.01 ---- SW1 ---- GND
  RX2-/+ o-- UART TXD, RXD -------- IC1
```

### 5.1 USB-C receptacle and debug pinout (J1)

| Contact          | USB-C name | Signal    | Goes to                          |
| ---------------- | ---------- | --------- | -------------------------------- |
| A4, A9, B4, B9   | VBUS       | VBUS      | D1 and R1                        |
| A1, A12, B1, B12 | GND        | GND       | ground, with the shell           |
| A5               | CC1        | CC1       | R2, 5.1 kΩ to ground             |
| B5               | CC2        | CC2       | R3, 5.1 kΩ to ground             |
| B2               | TX2+       | SWDIO     | D1, then module pin 27           |
| B3               | TX2−       | SWDCLK    | D1, then module pin 25           |
| A2               | TX1+       | nRESET    | JP1, then module pin 32          |
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
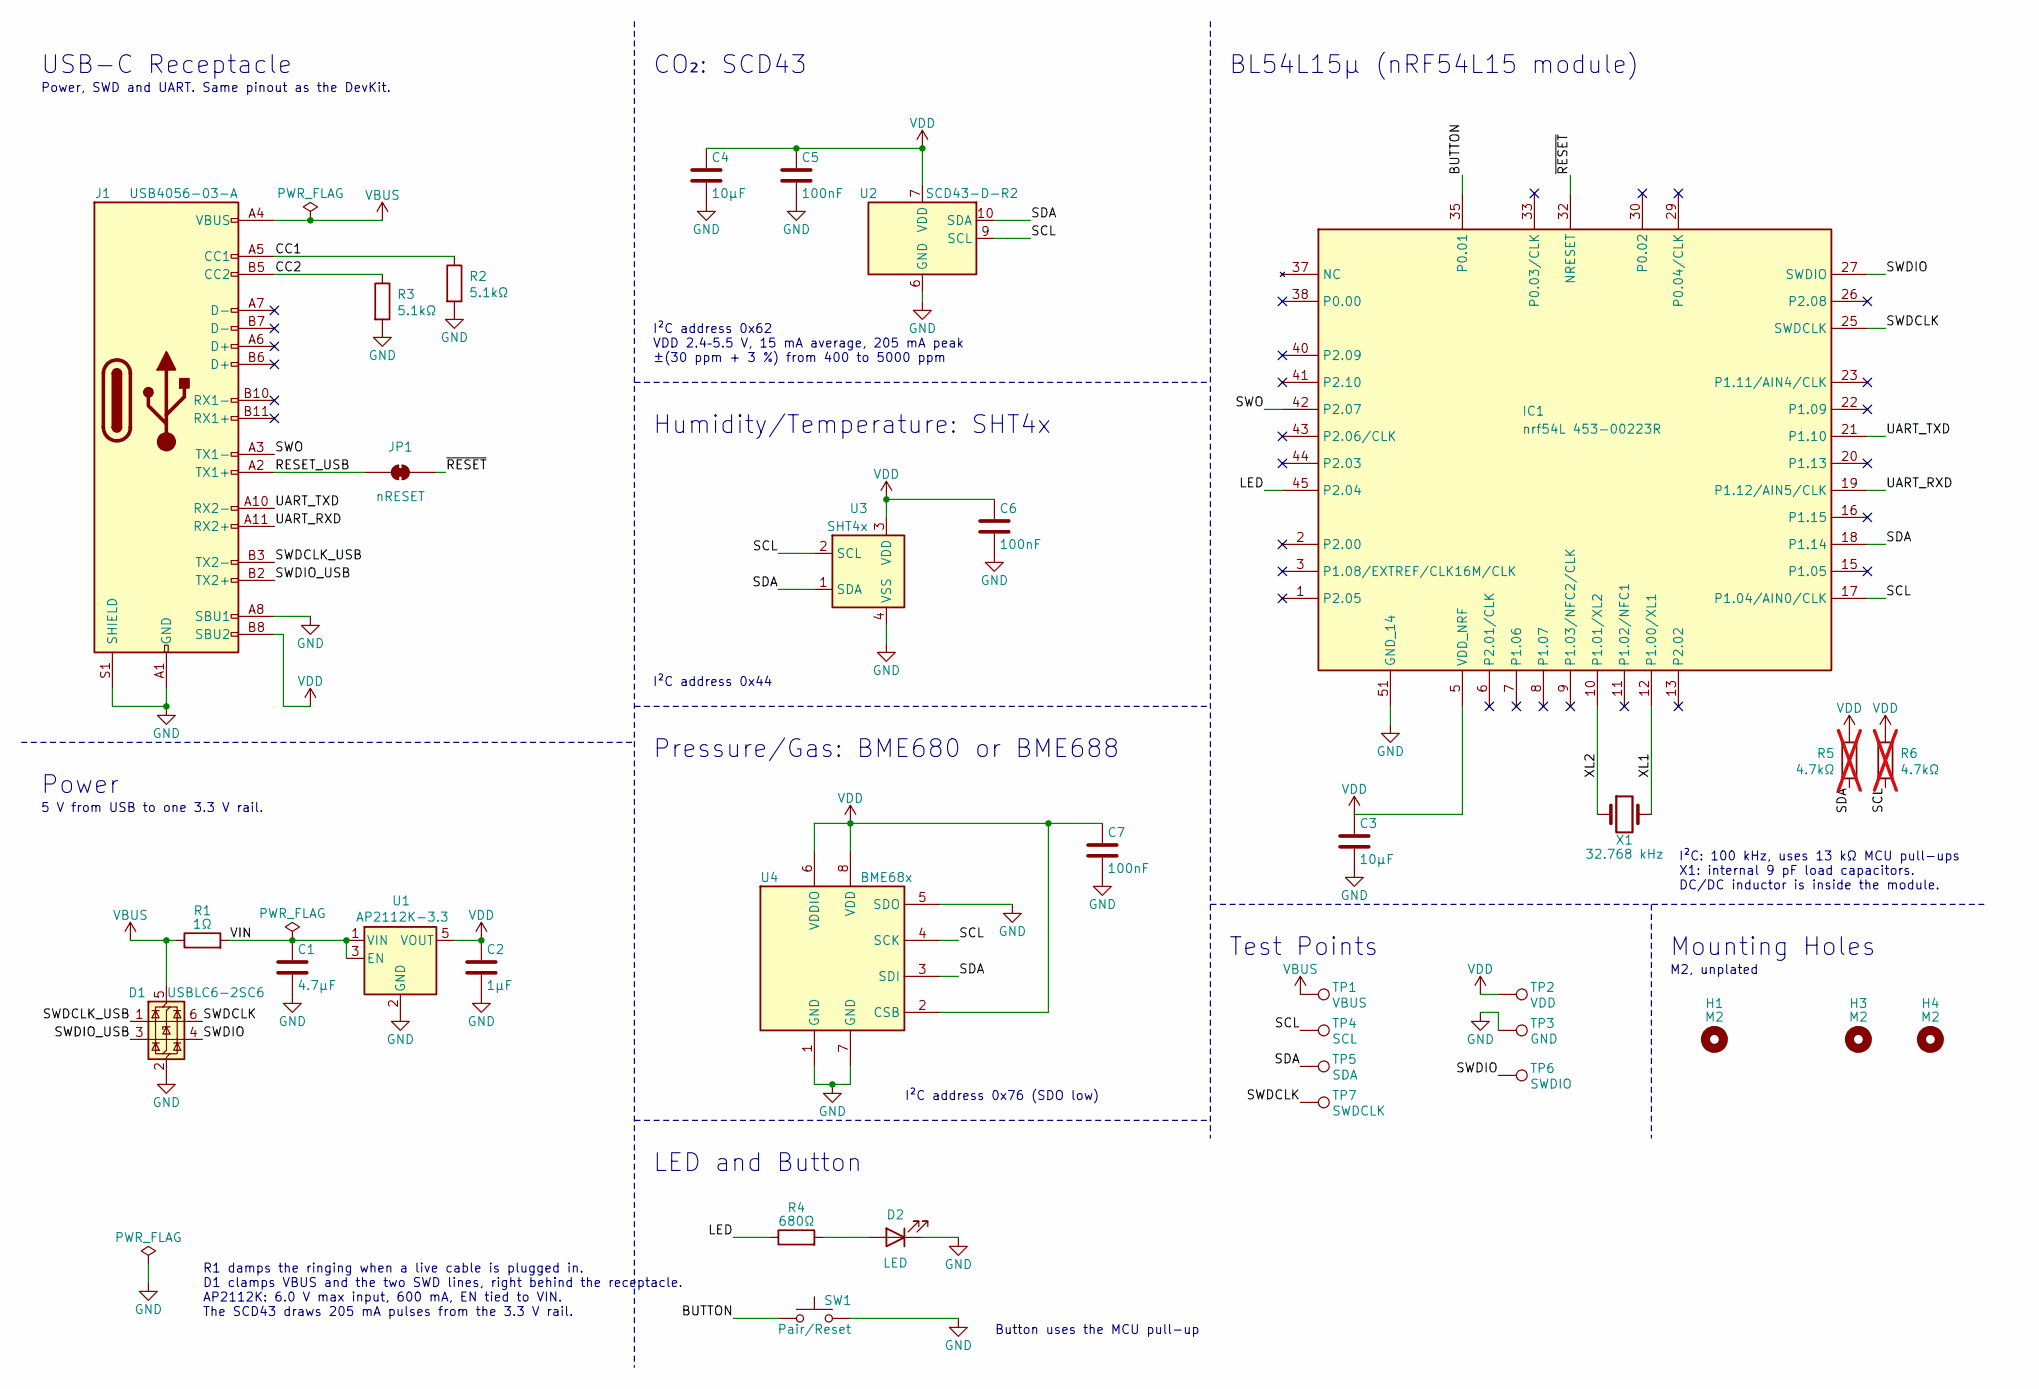
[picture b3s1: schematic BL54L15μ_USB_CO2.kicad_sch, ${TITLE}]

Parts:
C1: 4.7μF; C_0603_1608Metric; Part Number CL10A475KP8NNNC
C2: 1μF; C_0603_1608Metric
C3, C4: 10μF; C_0603_1608Metric; Part Number CL10A106KP8NNNC
C5, C6, C7: 100nF; C_0402_1005Metric; Part Number GRM155R61A104KA01J
D1: USBLC6-2SC6; SOT-23-6; Part Number USBLC6-2SC6
D2: LED; LED_0603_1608Metric
H1, H3, H4: M2; MountingHole_2.2mm_M2
IC1: nrf54L 453-00223R; 45300223R; Manufacturer_Part_Number 453-00223R
J1: USB4056-03-A; GCT_USB4056-03-A_REVA2; Part Number USB4056-03-A
JP1: nRESET; SolderJumper-2_P1.3mm_Bridged_RoundedPad1.0x1.5mm
R1: 1Ω; R_0603_1608Metric; Part Number RC0603FR-071RL
R2, R3: 5.1kΩ; R_0603_1608Metric; Part Number RC0603FR-075K1L
R4: 680Ω; R_0603_1608Metric
R5, R6: 4.7kΩ; R_0603_1608Metric; not fitted
SW1: Pair/Reset; SW_Push_SPST_NO_Alps_SKRK
TP1: VBUS; TestPoint_Pad_D1.0mm
TP2: VDD; TestPoint_Pad_D1.0mm
TP3: GND; TestPoint_Pad_D1.0mm
TP4: SCL; TestPoint_Pad_D1.0mm
TP5: SDA; TestPoint_Pad_D1.0mm
TP6: SWDIO; TestPoint_Pad_D1.0mm
TP7: SWDCLK; TestPoint_Pad_D1.0mm
U1: AP2112K-3.3; SOT-23-5; Part Number AP2112K-3.3TRG1
U2: SCD43-D-R2; Sensirion_SCD4x-1EP_10.1x10.1mm_P1.25mm_EP4.8x4.8mm; Part Number SCD43-D-R2
U3: SHT4x; Sensirion_DFN-4_1.5x1.5mm_P0.8mm_SHT4x_NoCentralPad; Part Number SHT45-AD1F-R2
U4: BME68x; Bosch_LGA-8_3x3mm_P0.8mm_ClockwisePinNumbering
X1: 32.768 kHz; XTAL_CM7V-T1A-LOW-ESR-32.768KHZ-9PF-20-TA-QC; Part Number CM7V-T1A-LOW-ESR-32.768KHZ-9PF-20-TA-QC

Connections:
/BUTTON: IC1.35 (P0.01), SW1.1
/CC1: J1.A5 (CC1), R2.1
/CC2: J1.B5 (CC2), R3.1
/LED: IC1.45 (P2.04), R4.1
/RESET_USB: J1.A2 (TX1+), JP1.1 (A)
/SCL: IC1.17 (P1.04/AIN0/CLK), R6.2, TP4.1 (1_1), U2.9 (SCL), U3.2 (SCL), U4.4 (SCK)
/SDA: IC1.18 (P1.14), R5.2, TP5.1 (1_1), U2.10 (SDA), U3.1 (SDA), U4.3 (SDI)
/SWDCLK: D1.6 (I/O1), IC1.25 (SWDCLK), TP7.1 (1_1)
/SWDCLK_USB: D1.1 (I/O1), J1.B3 (TX2-)
/SWDIO: D1.4 (I/O2), IC1.27 (SWDIO), TP6.1 (1_1)
/SWDIO_USB: D1.3 (I/O2), J1.B2 (TX2+)
/SWO: IC1.42 (P2.07), J1.A3 (TX1-)
/UART_RXD: IC1.19 (P1.12/AIN5/CLK), J1.A11 (RX2+)
/UART_TXD: IC1.21 (P1.10), J1.A10 (RX2-)
/VIN: C1.1, R1.2, U1.1 (VIN), U1.3 (EN)
/XL1: IC1.12 (P1.00/XL1), X1.2
/XL2: IC1.10 (P1.01/XL2), X1.1
/~RESET: IC1.32 (NRESET), JP1.2 (B)
GND: C1.2, C2.2, C3.2, C4.2, C5.2, C6.2, C7.2, D1.2 (GND), D2.1 (K), IC1.4 (GND_1), IC1.14 (GND_2), IC1.24 (GND_3), IC1.28 (GND_4), IC1.31 (GND_5), IC1.34 (GND_6), IC1.36 (GND_7), IC1.39 (GND_8), IC1.46 (GND_9), IC1.47 (GND_10), IC1.48 (GND_11), IC1.49 (GND_12), IC1.50 (GND_13), IC1.51 (GND_14), J1.A1 (GND), J1.A8 (SBU1), J1.A12 (GND), J1.B1 (GND), J1.B12 (GND), J1.S1 (SHIELD), R2.2, R3.2, SW1.2, TP3.1 (1_1), U1.2 (GND), U2.6 (GND), U2.20 (GND), U2.21 (GND), U3.4 (VSS), U4.1 (GND), U4.5 (SDO), U4.7 (GND)
unnamed: D2.2 (A), R4.2
VBUS: D1.5 (VBUS), J1.A4 (VBUS), J1.A9 (VBUS), J1.B4 (VBUS), J1.B9 (VBUS), R1.1, TP1.1 (1_1)
VDD: C2.1, C3.1, C4.1, C5.1, C6.1, C7.1, IC1.5 (VDD_NRF), J1.B8 (SBU2), R5.1, R6.1, TP2.1 (1_1), U1.5 (VOUT), U2.7 (VDD), U2.19 (VDD), U3.3 (VDD), U4.2 (CSB), U4.6 (VDDIO), U4.8 (VDD)

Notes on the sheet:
Power
I²C address 0x76 (SDO low)
USB-C Receptacle
Mounting Holes
Button uses the MCU pull-up
Power, SWD and UART. Same pinout as the DevKit.
I²C: 100 kHz, uses 13 kΩ MCU pull-ups X1: internal 9 pF load capacitors. DC/DC inductor is inside the module.
R1 damps the ringing when a live cable is plugged in. D1 clamps VBUS and the two SWD lines, right behind the receptacle. AP2112K: 6.0 V max input, 600 mA, EN tied to VIN. The SCD43 draws 205 mA pulses from the 3.3 V rail.
M2, unplated
Humidity/Temperature: SHT4x
Test Points
5 V from USB to one 3.3 V rail.
I²C address 0x62 VDD 2.4–5.5 V, 15 mA average, 205 mA peak ±(30 ppm + 3 %) from 400 to 5000 ppm
Pressure/Gas: BME680 or BME688
I²C address 0x44
CO₂: SCD43
LED and Button
BL54L15μ (nRF54L15 module)
